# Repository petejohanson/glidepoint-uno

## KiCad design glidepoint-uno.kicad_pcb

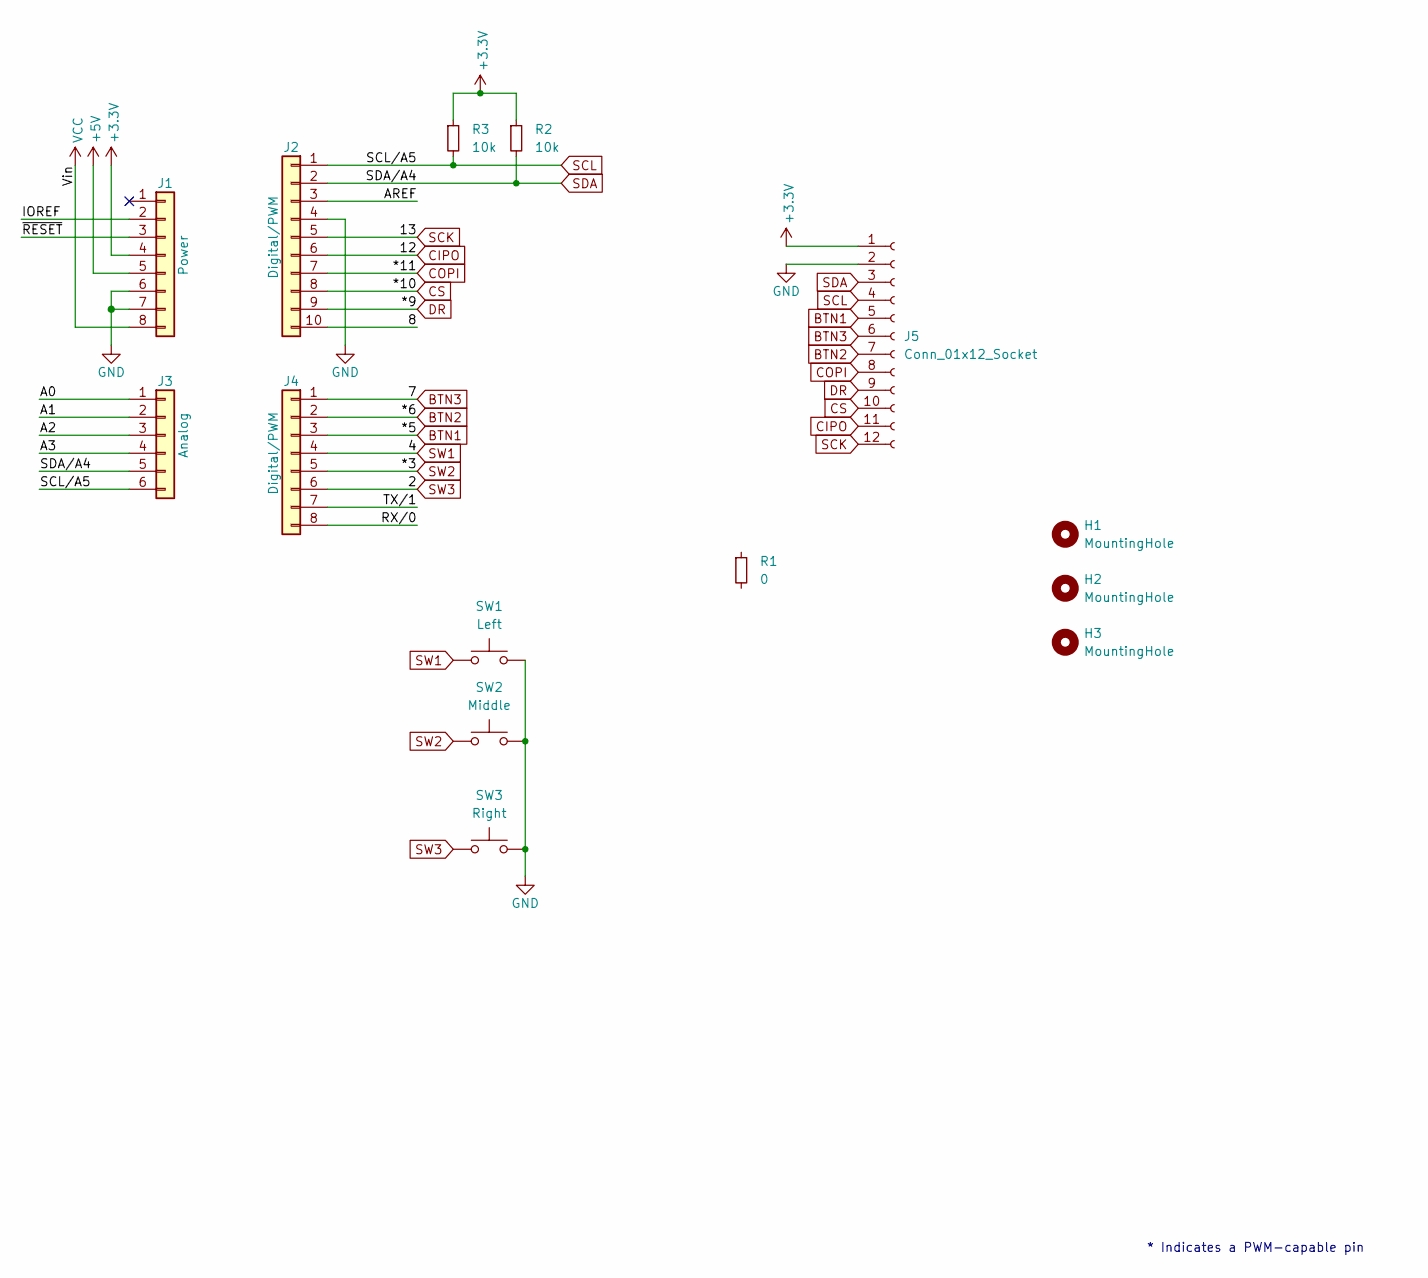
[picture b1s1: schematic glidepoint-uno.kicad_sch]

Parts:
H1, H2, H3: MountingHole; MountingHole_M2_Pad_NonPTH_TopOnly; LCSC C2916319
J1: Power; PinSocket_1x08_P2.54mm_Vertical
J2: Digital/PWM; PinSocket_1x10_P2.54mm_Vertical
J3: Analog; PinSocket_1x06_P2.54mm_Vertical
J4: Digital/PWM; PinSocket_1x08_P2.54mm_Vertical
J5: Conn_01x12_Socket; FPC-SMD_FPC05012-09200-.5mm-rev; LCSC C479750
R1: 0; R_0805_2012Metric; LCSC C17414
R2, R3: 10k; R_0805_2012Metric
SW1: Left; SW_SKSTAAE010; LCSC C202379
SW2: Middle; SW_SKSTAAE010; LCSC C202379
SW3: Right; SW_SKSTAAE010; LCSC C202379

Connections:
+3V3: J1.4, J5.1, R2.1, R3.1
+5V: J1.5
/8: J2.10
/A0: J3.1
/A1: J3.2
/A2: J3.3
/A3: J3.4
/AREF: J2.3
/IOREF: J1.2
/RX/0: J4.8
/TX/1: J4.7
/~RESET: J1.3
BTN1: J4.3, J5.5
BTN2: J4.2, J5.7
BTN3: J4.1, J5.6
CIPO: J2.6, J5.11
COPI: J2.7, J5.8
CS: J2.8, J5.10
DR: J2.9, J5.9
GND: J1.6, J1.7, J2.4, J5.2, SW1.2, SW2.2, SW3.2
SCK: J2.5, J5.12
SCL: J2.1, J3.6, J5.4, R3.2
SDA: J2.2, J3.5, J5.3, R2.2
SW1: J4.4, SW1.1
SW2: J4.5, SW2.1
SW3: J4.6, SW3.1
VCC: J1.8

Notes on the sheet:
* Indicates a PWM-capable pin

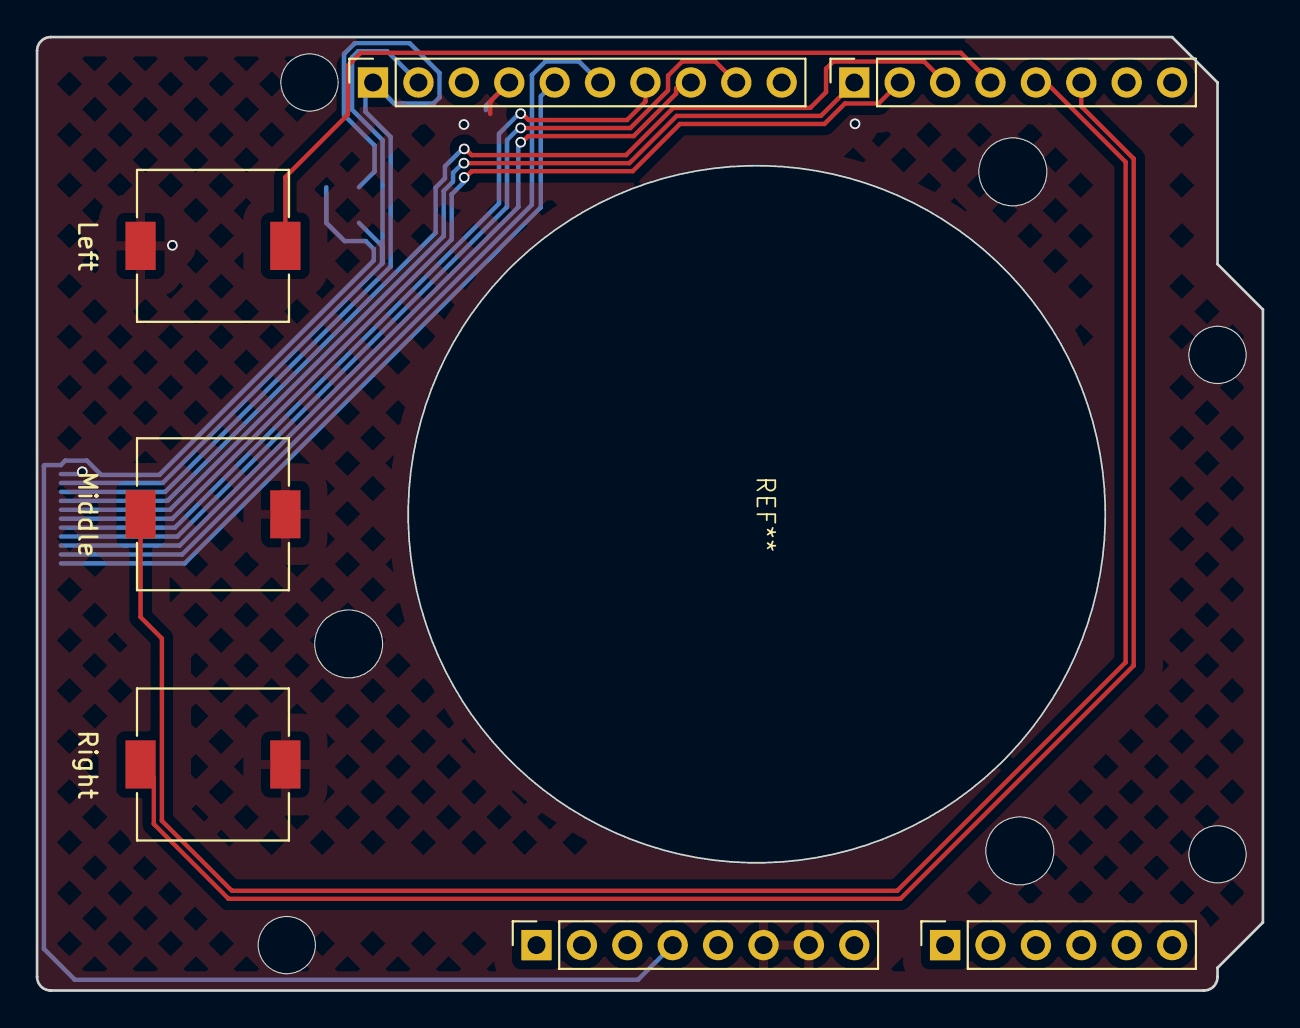
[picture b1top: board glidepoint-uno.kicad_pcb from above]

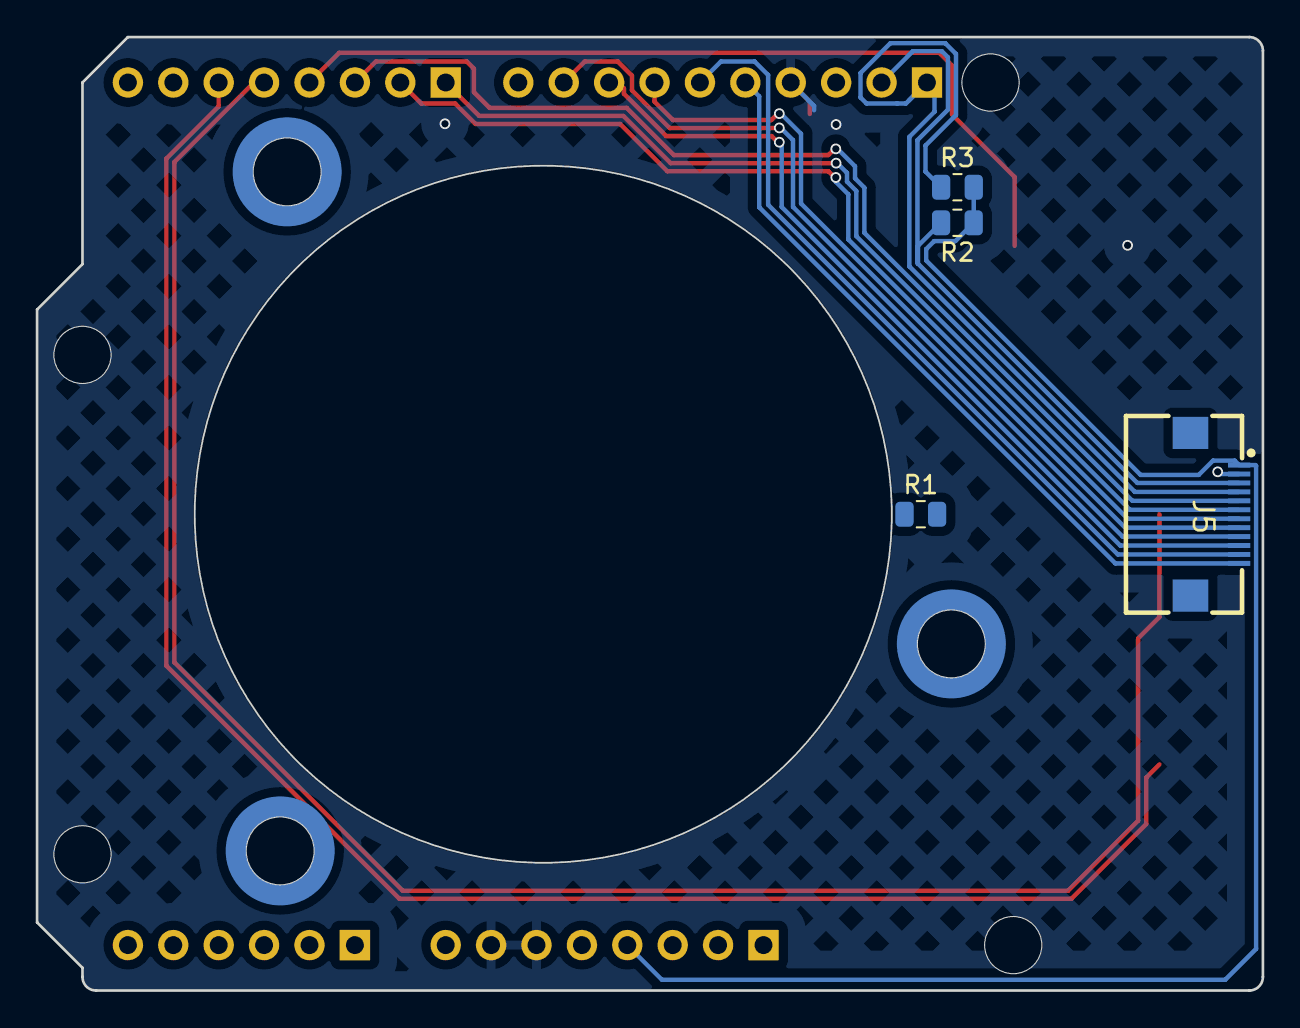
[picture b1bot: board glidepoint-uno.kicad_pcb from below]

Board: 2 copper layers, 68.6 x 53.3 mm, 18 parts (7 on the bottom side), 15 nets.

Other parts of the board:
MH1, MH2, MH3, MH4: MountingHole_3.2mm

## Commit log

2023-06-21 Initial work on GlidePoint Uno.
2023-06-21 Fixes to bottom placement in pick and place.
2023-06-21 Automate exporting.
2023-06-21 Routing tweaks.
2023-06-21 Add LICENSE.
2023-06-21 Add 3 mounting holes.
2023-06-21 Ignore a few generated files/dirs.
2023-06-21 A bit more 3d model/rendering for the GlidePoint.
2023-06-21 Fix the filenames for archive of kibot export.
2023-06-22 Add i2c pull-ups, switch to Alps tactile buttons.
